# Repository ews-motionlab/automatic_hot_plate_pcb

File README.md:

# README #

This repository contains schematic and PCB files for the controller created to use a hot plate
as a PCB reflow solder station.

### How do I get set up? ###

* The design files contained at the repository are created with EAGLE 9.5 so it requires EAGLE.

### Who do I talk to? ###

* Pleae talk to Raul Quesada Navarro @ raquenaengineering for more information 
* Raul.quesadanavarro@raquenaengineering.com

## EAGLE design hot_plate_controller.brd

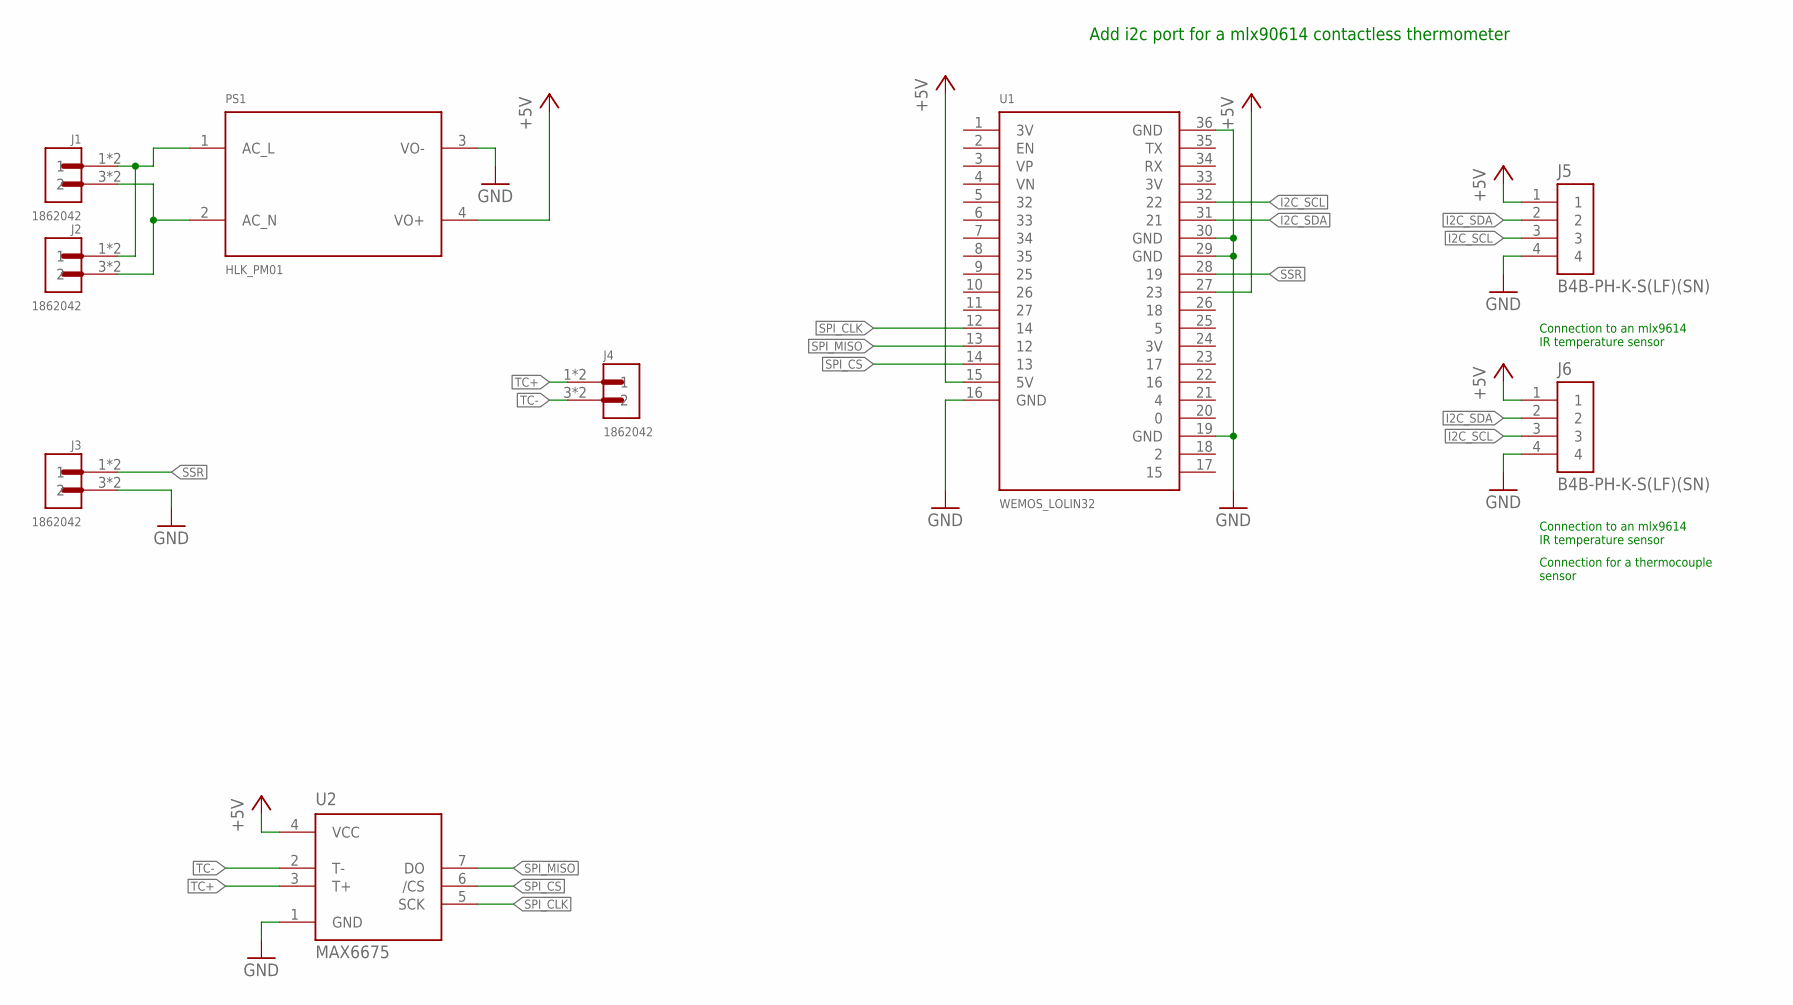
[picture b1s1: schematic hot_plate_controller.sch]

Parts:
J1, J2, J3, J4: 1862042; PHOENIX_1862042
J5, J6: B4B-PH-K-S(LF)(SN); JST_B4B-PH-K-S(LF)(SN)
PS1: HLK_PM01; HLK_PM
U1: WEMOS_LOLIN32
U2: MAX6675; SO08

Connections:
!SPI_CS: U1.14 (13), U2.6 (/CS)
+5V: J5.1, J6.1, PS1.4 (VO+), U1.15 (5V), U1.27 (23), U2.4 (VCC)
AC_L: J1.1, J1.2 (1), J2.1, J2.2 (1), PS1.1 (AC_L)
AC_N: J1.3 (2), J1.4 (2), J2.3 (2), J2.4 (2), PS1.2 (AC_N)
GND: J3.3 (2), J3.4 (2), J5.4, J6.4, PS1.3 (VO-), U1.16 (GND), U1.19 (GND), U1.29 (GND), U1.30 (GND), U1.36 (GND), U2.1 (GND)
I2C_SCL: J5.3, J6.3, U1.32 (22)
I2C_SDA: J5.2, J6.2, U1.31 (21)
SPI_CLK: U1.12 (14), U2.5 (SCK)
SPI_MISO: U1.13 (12), U2.7 (DO)
SSR: J3.1, J3.2 (1), U1.28 (19)
TC+: J4.1, J4.2 (1), U2.3 (T+)
TC-: J4.3 (2), J4.4 (2), U2.2 (T-)

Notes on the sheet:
Add i2c port for a mlx90614 contactless thermometer
Connection to an mlx9614 IR temperature sensor
Connection for a thermocouple sensor

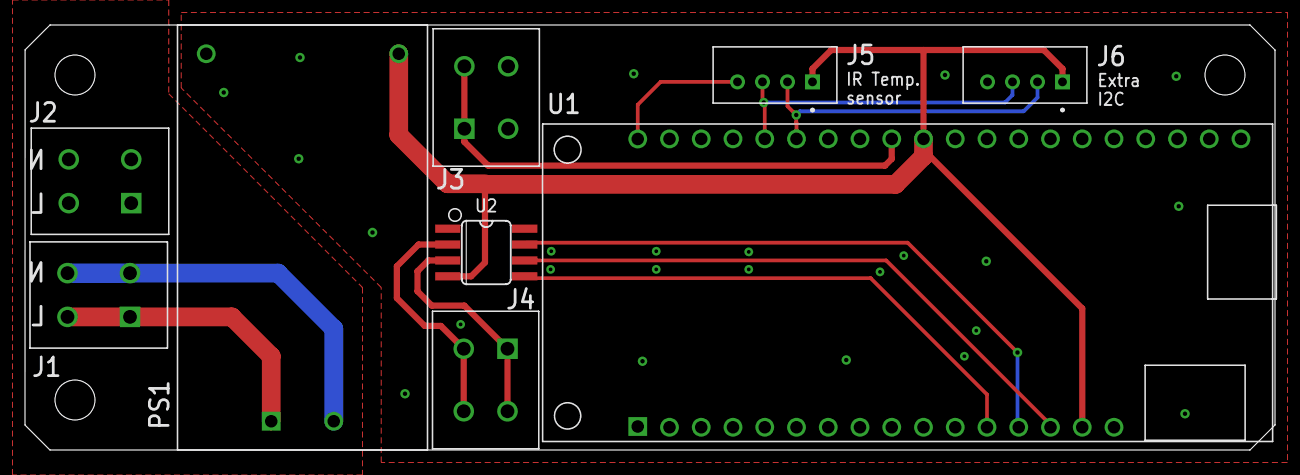
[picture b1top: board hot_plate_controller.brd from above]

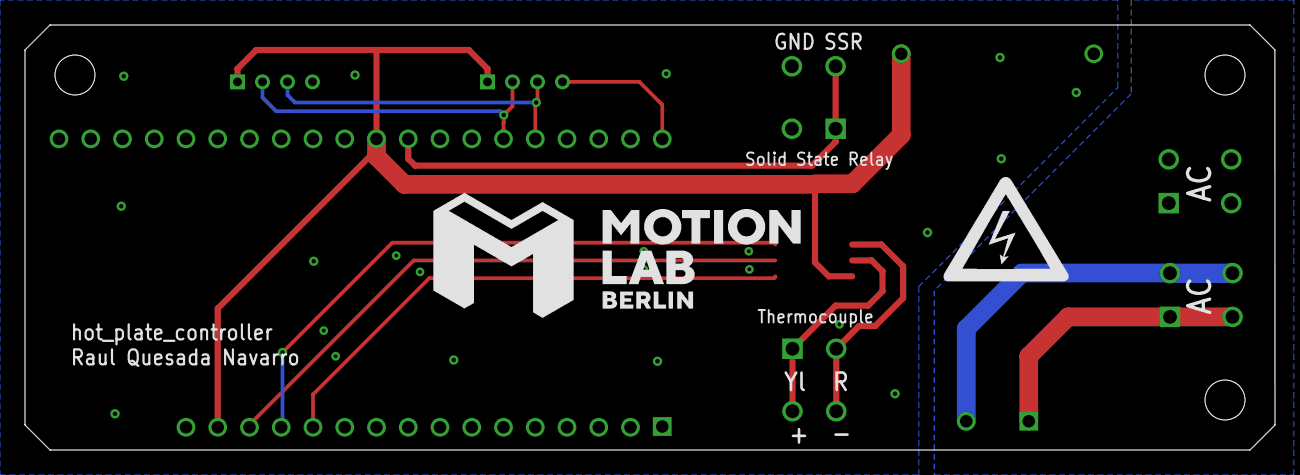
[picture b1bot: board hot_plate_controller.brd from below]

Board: 2 copper layers, 100.0 x 34.0 mm, 11 parts (2 on the bottom side), 12 nets.

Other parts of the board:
U$1: ML_LOGO_TEXT_10MM
U$2: HIGH_VOLTAGE_LOGO_10MM

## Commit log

2019-11-19 Add files on the previous private repository, containing the first iteration already sent to manufacture.
2019-11-22 - Add MotionLab logo. - Add separated power planes on AC side. - Add high voltage symbol. - place all texts in the right side with the right rotation. - add markings for SSR, thermocouple, i2c and AC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
